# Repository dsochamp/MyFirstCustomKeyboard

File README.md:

# MyFirstCustomKeyboard

## TL;DR

This is my first custom keyboard build, as an introductory project to PCB and Hardware Design and getting use to making projects like these. This is a 60% mechanical keyboard, using Brown MX Switch Keys (PCB can support other types including Cherry MX with **Hot-swap not included**) and a Raspberry Pi Pico W as the brains. It also features a charging system, using a LiPo battery paired with a MCP73831-2-OT charging controller for battery health and monitoring. The keyboard connects via Bluetooth (firmware will be available) and charges using USB-C. 

## Software used

KiCad was used in PCB design to create the schematic and PCB design as well as generating the manufacturing files. An online ```.dxf``` file converter was used to convert the images to Silkscreen. I then used Onshape (Web-based CAD tool) to design teh case for the keyboard. Firmware will be added later.

## PCB

The PCB design includes 50 keys, 54 resistors, a MCP73831-2-OT charging controller, USB-C input and a Raspberry Pi Pico W. Here are some images of the PCB:

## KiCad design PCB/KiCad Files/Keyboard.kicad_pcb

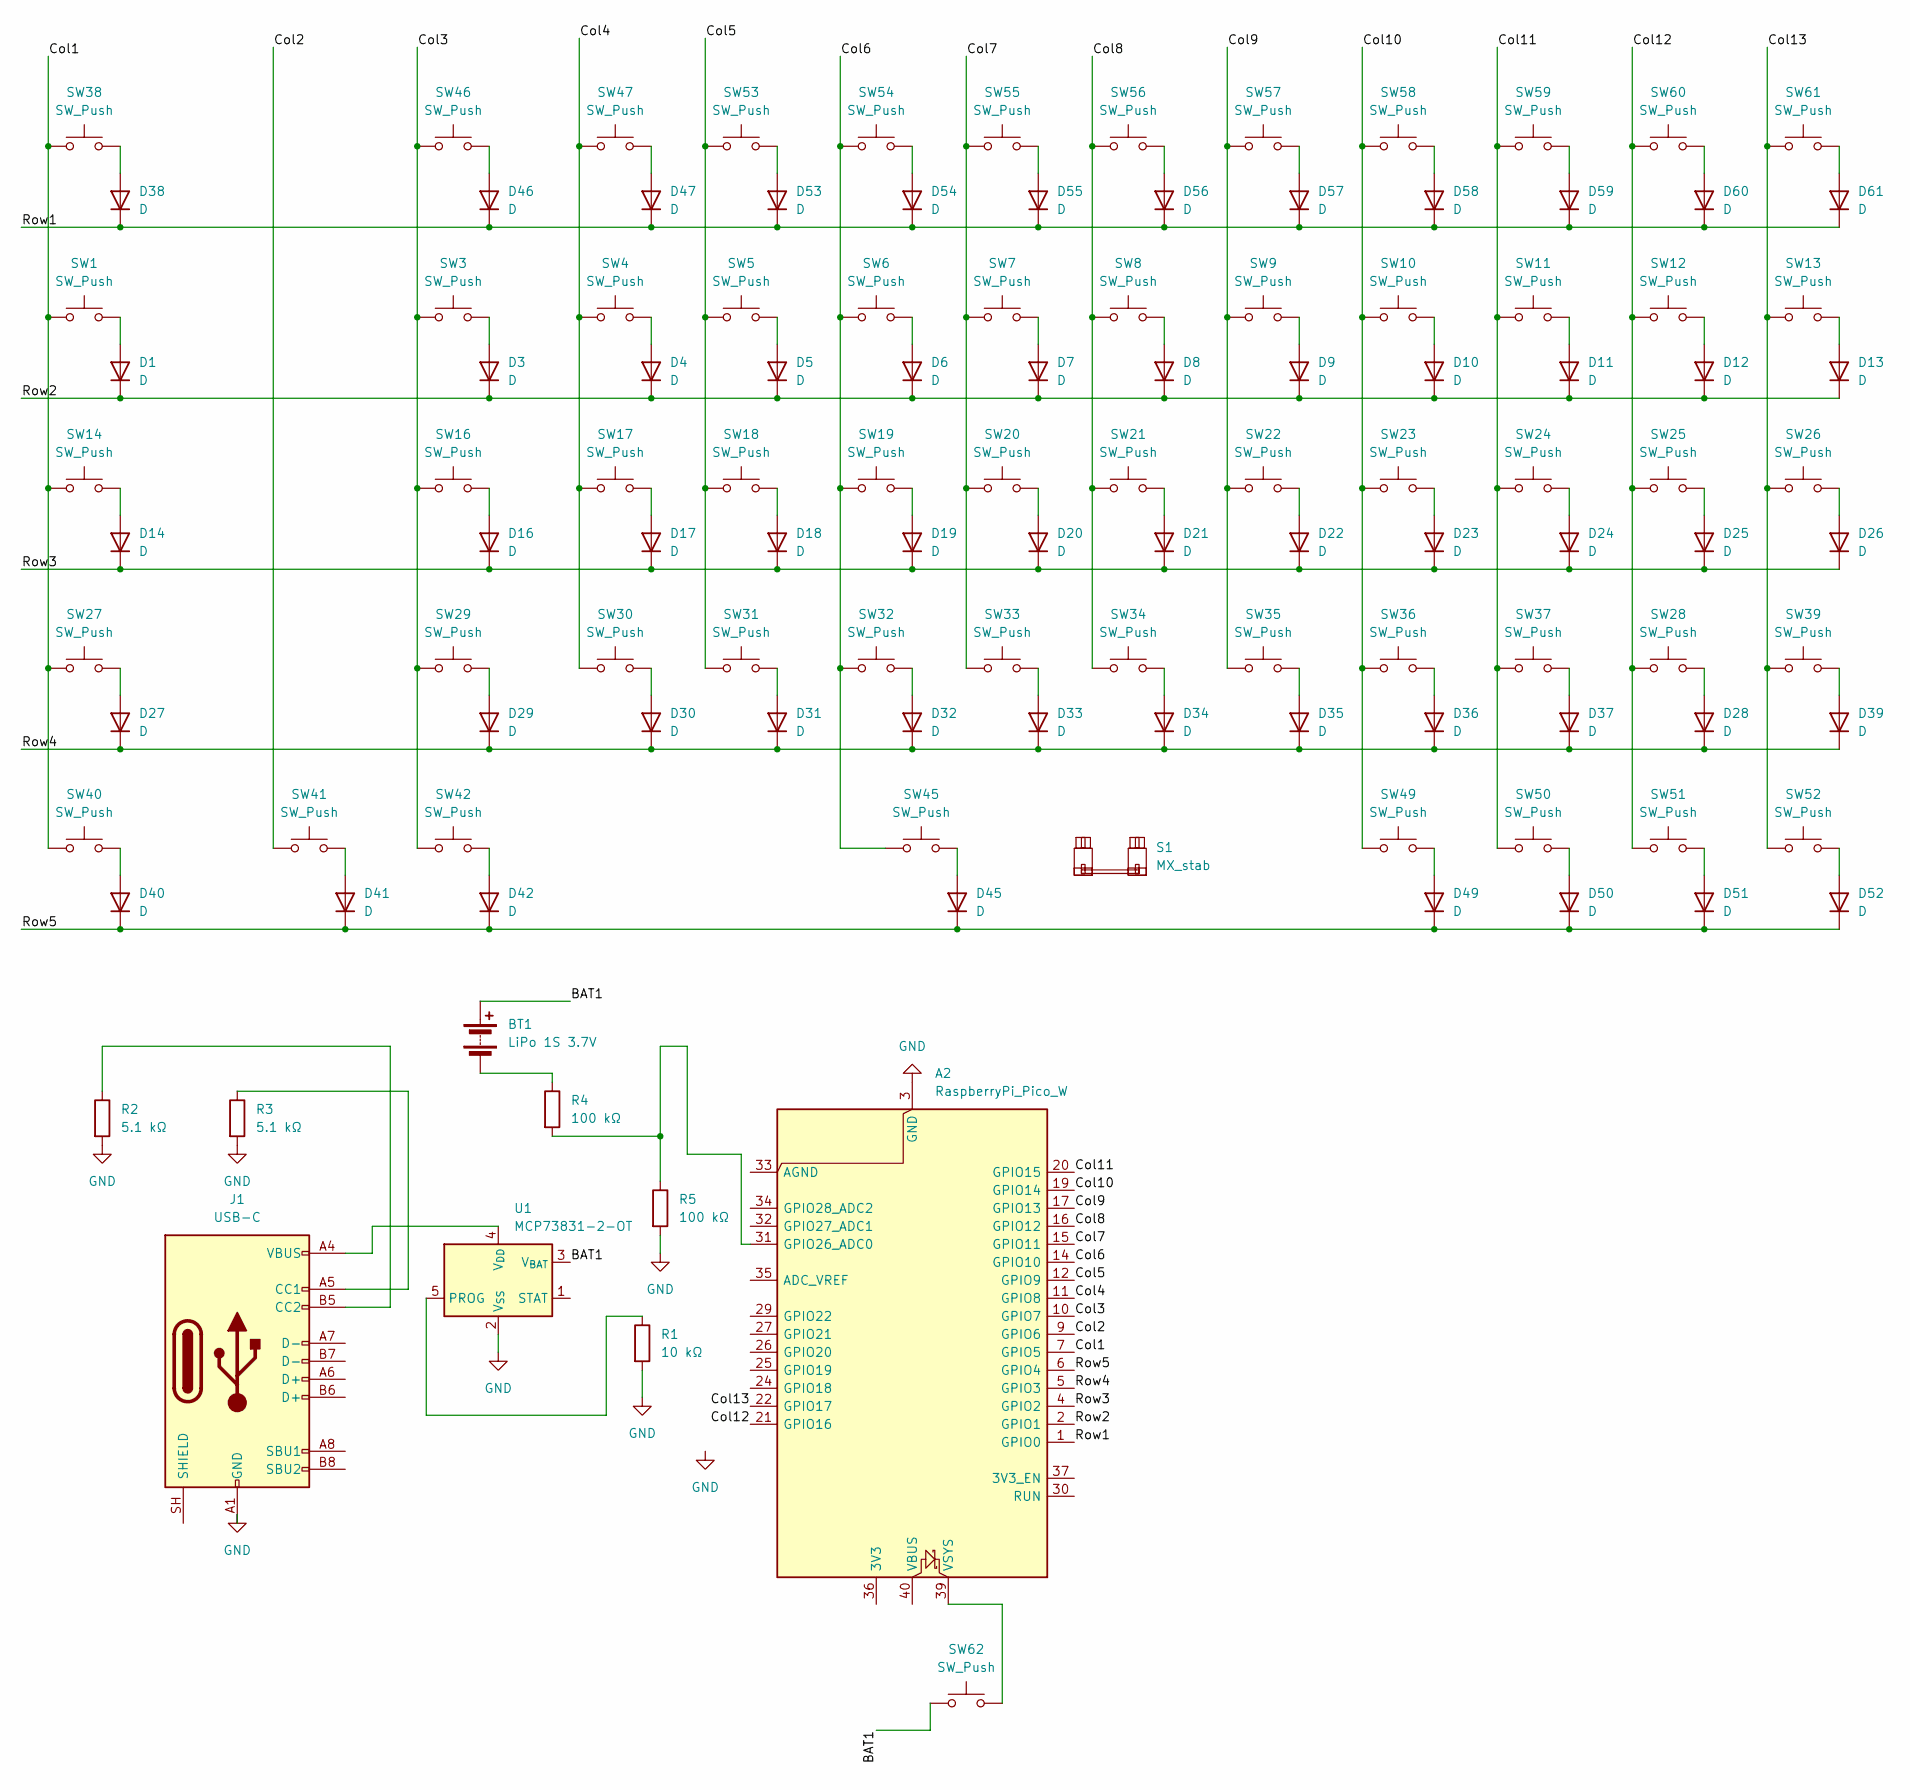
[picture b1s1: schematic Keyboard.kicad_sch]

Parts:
A2: RaspberryPi_Pico_W; RaspberryPi_Pico_W_SMD_HandSolder
BT1: LiPo 1S 3.7V
D1, D3, D4, D5, D6, D7, D8, D9, D10, D11, D12, D13, D14, D16, D17, D18, D19, D20, D21, D22, D23, D24, D25, D26, D27, D28, D29, D30, D31, D32, D33, D34, D35, D36, D37, D38, D39, D40, D41, D42, D45, D46, D47, D49, D50, D51, D52, D53, D54, D55, D56, D57, D58, D59, D60, D61: D; D_DO-35_SOD27_P7.62mm_Horizontal
J1: USB-C; USB_C_Receptacle_GCT_USB4105-xx-A_16P_TopMnt_Horizontal
R1: 10 kΩ; R_0805_2012Metric
R2, R3: 5.1 kΩ; R_0805_2012Metric
R4, R5: 100 kΩ; R_0805_2012Metric
S1: MX_stab; STAB_MX_6u
SW1, SW13: SW_Push; SW_MX_1.5u
SW3, SW4, SW5, SW6, SW7, SW8, SW9, SW10, SW11, SW12, SW16, SW17, SW18, SW19, SW20, SW21, SW22, SW23, SW24, SW25, SW28, SW29, SW30, SW31, SW32, SW33, SW34, SW35, SW36, SW37, SW40, SW41, SW42, SW45, SW46, SW47, SW49, SW50, SW51, SW52, SW53, SW54, SW55, SW56, SW57, SW58, SW59, SW60, SW62: SW_Push; SW_MX_1u
SW14, SW39, SW61: SW_Push; SW_MX_1.25u
SW26, SW27, SW38: SW_Push; SW_MX_1.75u
U1: MCP73831-2-OT; SOT-23-5

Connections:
/BAT1: BT1.1 (+), SW62.1, U1.3 (V_{BAT})
/Col1: A2.7 (GPIO5), SW1.1, SW14.1, SW27.1, SW38.1, SW40.1
/Col2: A2.9 (GPIO6), SW41.1
/Col3: A2.10 (GPIO7), SW3.1, SW16.1, SW29.1, SW42.1, SW46.1
/Col4: A2.11 (GPIO8), SW4.1, SW17.1, SW30.1, SW47.1
/Col5: A2.12 (GPIO9), SW5.1, SW18.1, SW31.1, SW53.1
/Col6: A2.14 (GPIO10), SW6.1, SW19.1, SW32.1, SW45.1, SW54.1
/Col7: A2.15 (GPIO11), SW7.1, SW20.1, SW33.1, SW55.1
/Col8: A2.16 (GPIO12), SW8.1, SW21.1, SW34.1, SW56.1
/Col9: A2.17 (GPIO13), SW9.1, SW22.1, SW35.1, SW57.1
/Col10: A2.19 (GPIO14), SW10.1, SW23.1, SW36.1, SW49.1, SW58.1
/Col11: A2.20 (GPIO15), SW11.1, SW24.1, SW37.1, SW50.1, SW59.1
/Col12: A2.21 (GPIO16), SW12.1, SW25.1, SW28.1, SW51.1, SW60.1
/Col13: A2.22 (GPIO17), SW13.1, SW26.1, SW39.1, SW52.1, SW61.1
/Row1: A2.1 (GPIO0), D38.1 (K), D46.1 (K), D47.1 (K), D53.1 (K), D54.1 (K), D55.1 (K), D56.1 (K), D57.1 (K), D58.1 (K), D59.1 (K), D60.1 (K), D61.1 (K)
/Row2: A2.2 (GPIO1), D1.1 (K), D3.1 (K), D4.1 (K), D5.1 (K), D6.1 (K), D7.1 (K), D8.1 (K), D9.1 (K), D10.1 (K), D11.1 (K), D12.1 (K), D13.1 (K)
/Row3: A2.4 (GPIO2), D14.1 (K), D16.1 (K), D17.1 (K), D18.1 (K), D19.1 (K), D20.1 (K), D21.1 (K), D22.1 (K), D23.1 (K), D24.1 (K), D25.1 (K), D26.1 (K)
/Row4: A2.5 (GPIO3), D27.1 (K), D28.1 (K), D29.1 (K), D30.1 (K), D31.1 (K), D32.1 (K), D33.1 (K), D34.1 (K), D35.1 (K), D36.1 (K), D37.1 (K), D39.1 (K)
/Row5: A2.6 (GPIO4), D40.1 (K), D41.1 (K), D42.1 (K), D45.1 (K), D49.1 (K), D50.1 (K), D51.1 (K), D52.1 (K)
GND: A2.3 (GND), A2.8 (GND), A2.13 (GND), A2.18 (GND), A2.23 (GND), A2.28 (GND), A2.38 (GND), J1.A1 (GND), J1.A12 (GND), J1.B1 (GND), J1.B12 (GND), R1.2, R2.2, R3.2, R5.2, U1.2 (V_{SS})
unnamed: A2.31 (GPIO26_ADC0), R4.2, R5.1
unnamed: A2.39 (VSYS), SW62.2
unnamed: BT1.2 (-), R4.1
unnamed: D1.2 (A), SW1.2
unnamed: D3.2 (A), SW3.2
unnamed: D4.2 (A), SW4.2
unnamed: D5.2 (A), SW5.2
unnamed: D6.2 (A), SW6.2
unnamed: D7.2 (A), SW7.2
unnamed: D8.2 (A), SW8.2
unnamed: D9.2 (A), SW9.2
unnamed: D10.2 (A), SW10.2
unnamed: D11.2 (A), SW11.2
unnamed: D12.2 (A), SW12.2
unnamed: D13.2 (A), SW13.2
unnamed: D14.2 (A), SW14.2
unnamed: D16.2 (A), SW16.2
unnamed: D17.2 (A), SW17.2
unnamed: D18.2 (A), SW18.2
unnamed: D19.2 (A), SW19.2
unnamed: D20.2 (A), SW20.2
unnamed: D21.2 (A), SW21.2
unnamed: D22.2 (A), SW22.2
unnamed: D23.2 (A), SW23.2
unnamed: D24.2 (A), SW24.2
unnamed: D25.2 (A), SW25.2
unnamed: D26.2 (A), SW26.2
unnamed: D27.2 (A), SW27.2
unnamed: D28.2 (A), SW28.2
unnamed: D29.2 (A), SW29.2
unnamed: D30.2 (A), SW30.2
unnamed: D31.2 (A), SW31.2
unnamed: D32.2 (A), SW32.2
unnamed: D33.2 (A), SW33.2
unnamed: D34.2 (A), SW34.2
unnamed: D35.2 (A), SW35.2
unnamed: D36.2 (A), SW36.2
unnamed: D37.2 (A), SW37.2
unnamed: D38.2 (A), SW38.2
unnamed: D39.2 (A), SW39.2
unnamed: D40.2 (A), SW40.2
unnamed: D41.2 (A), SW41.2
unnamed: D42.2 (A), SW42.2
unnamed: D45.2 (A), SW45.2
unnamed: D46.2 (A), SW46.2
unnamed: D47.2 (A), SW47.2
unnamed: D49.2 (A), SW49.2
unnamed: D50.2 (A), SW50.2
unnamed: D51.2 (A), SW51.2
unnamed: D52.2 (A), SW52.2
unnamed: D53.2 (A), SW53.2
unnamed: D54.2 (A), SW54.2
unnamed: D55.2 (A), SW55.2
unnamed: D56.2 (A), SW56.2
unnamed: D57.2 (A), SW57.2
unnamed: D58.2 (A), SW58.2
unnamed: D59.2 (A), SW59.2
unnamed: D60.2 (A), SW60.2
unnamed: D61.2 (A), SW61.2
unnamed: J1.A5 (CC1), R3.1
unnamed: J1.B5 (CC2), R2.1
unnamed: R1.1, U1.5 (PROG)
unnamed: J1.A4 (VBUS), J1.A9 (VBUS), J1.B4 (VBUS), J1.B9 (VBUS), U1.4 (V_{DD})

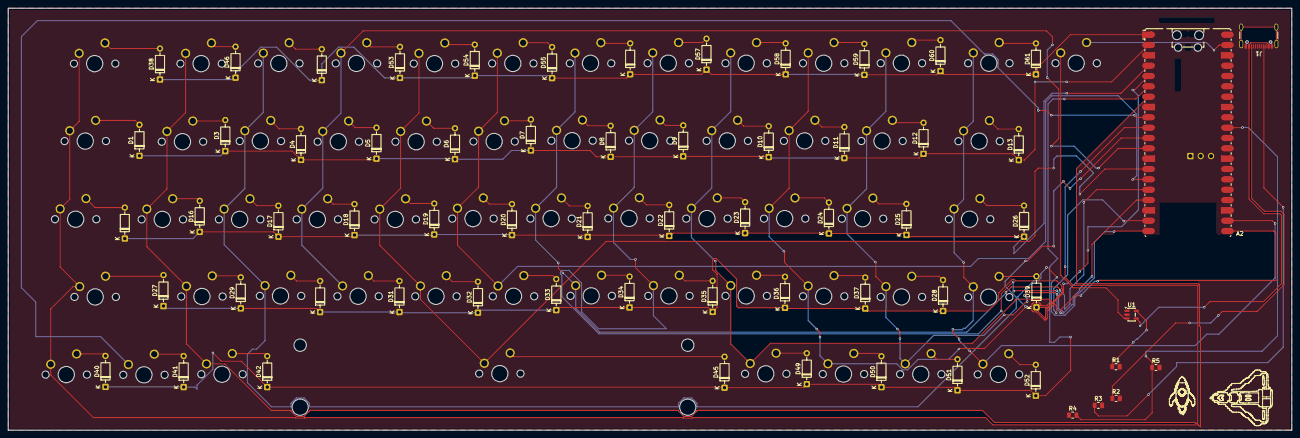
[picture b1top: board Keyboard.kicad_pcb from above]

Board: 2 copper layers, 315.4 x 103.7 mm, 122 parts (0 on the bottom side), 82 nets.
